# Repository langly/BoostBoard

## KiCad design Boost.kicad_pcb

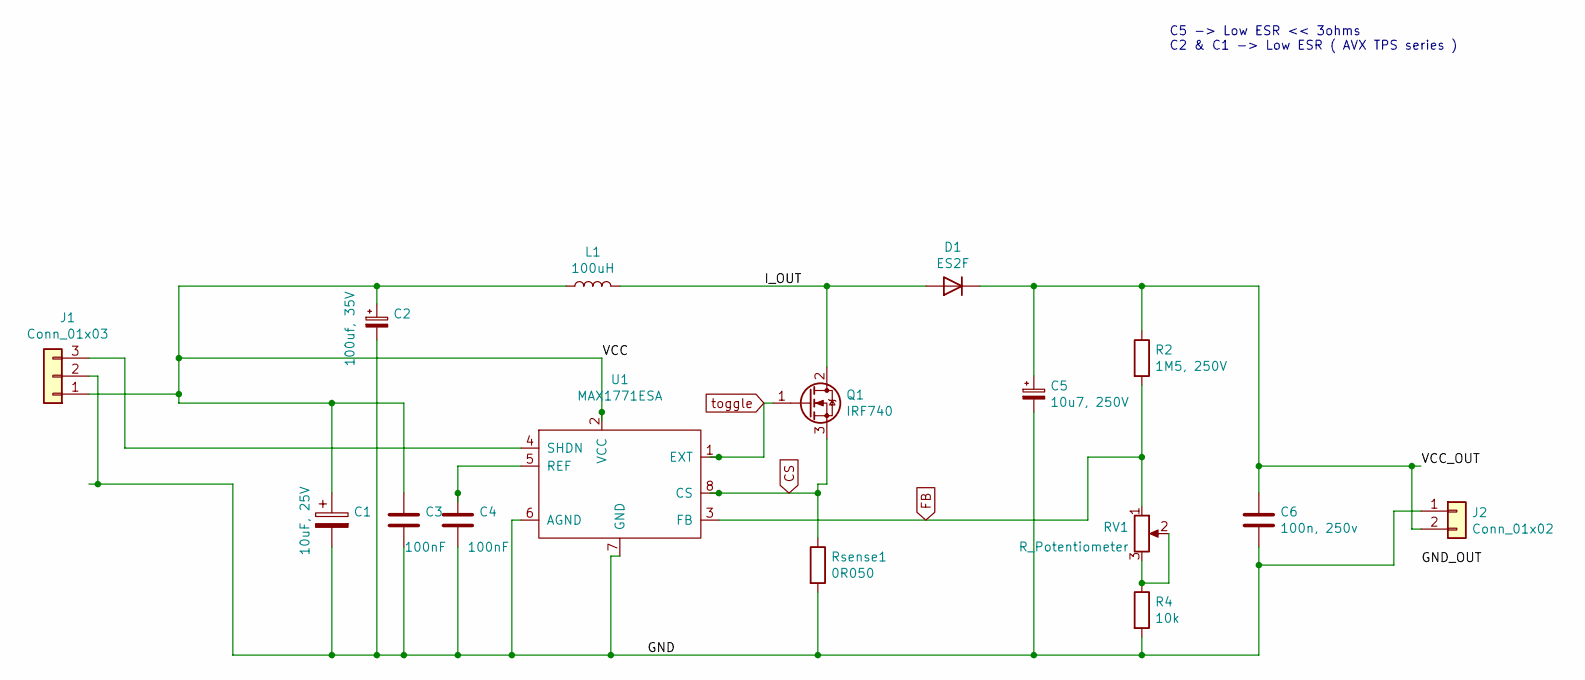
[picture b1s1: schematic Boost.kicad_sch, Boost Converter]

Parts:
C1: 10uF, 25V; CP_EIA-3528-21_Kemet-B_Pad1.50x2.35mm_HandSolder
C2: 100uf, 35V; CP_EIA-7361-38_AVX-V_Pad2.18x3.30mm_HandSolder
C3, C4: 100nF; C_0805_2012Metric
C5: 10u7, 250V; Panasonic-G17
C6: 100n, 250v; ECWU_B
D1: ES2F; D_SMB_Handsoldering
J1: Conn_01x03; 691412320003
J2: Conn_01x02; 691412320002
L1: 100uH; B82479A1
Q1: IRF740; TO-263-3_TabPin2
R2: 1M5, 250V; R_2512_6332Metric
R4: 10k; R_0805_2012Metric_Pad1.20x1.40mm_HandSolder
RV1: R_Potentiometer; 3214W1502E
Rsense1: 0R050; R_2010_5025Metric_Pad1.40x2.65mm_HandSolder
U1: MAX1771ESA; SOIC-8-1EP_3.9x4.9mm_P1.27mm_EP2.29x3mm

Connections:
/GND: C1.2, C2.2, C3.2, C4.2, C5.2, C6.2, J1.2, J2.1, R4.2, Rsense1.2, U1.6 (AGND), U1.7 (GND)
/I_OUT: D1.2 (A), L1.2, Q1.2 (D)
/VCC: C1.1, C2.1, C3.1, J1.1, L1.1, U1.2 (VCC)
/VCC_OUT: C5.1, C6.1, D1.1 (K), J2.2, R2.1
CS: Q1.3 (S), Rsense1.1, U1.8 (CS)
FB: R2.2, RV1.1, U1.3 (FB)
unnamed: J1.3, U1.4 (SHDN)
unnamed: R4.1, RV1.2, RV1.3
unnamed: C4.1, U1.5 (REF)
toggle: Q1.1 (G), U1.1 (EXT)

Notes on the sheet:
C5 -> Low ESR << 3ohms C2 & C1 -> Low ESR ( AVX TPS series )

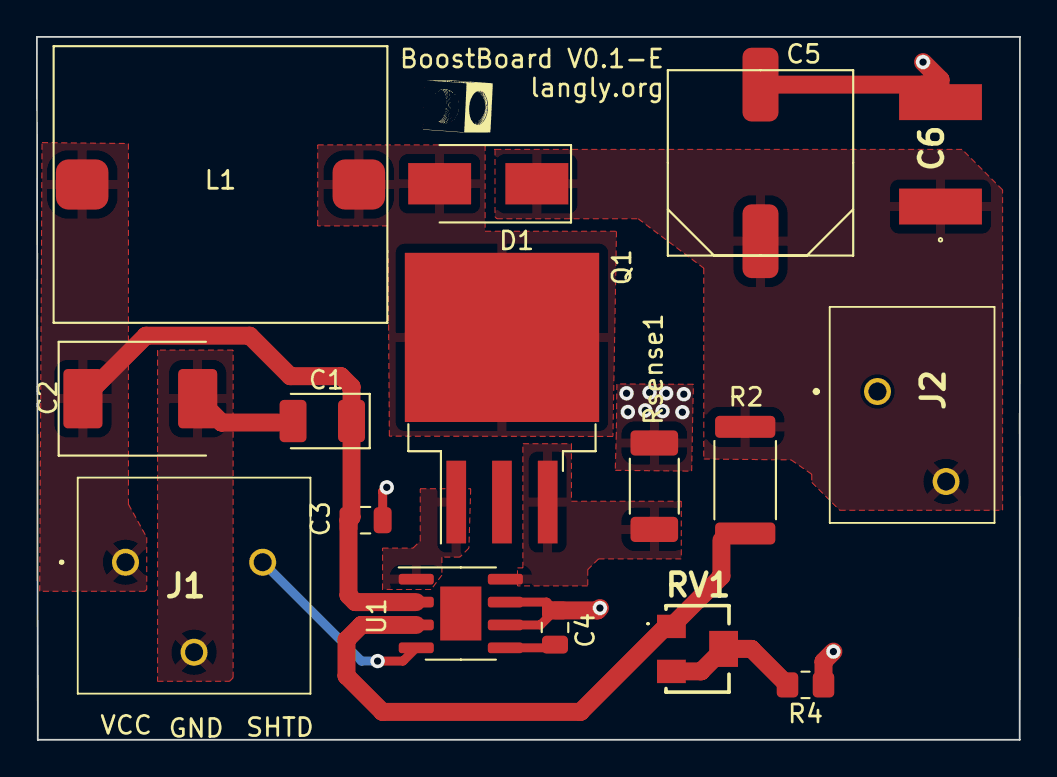
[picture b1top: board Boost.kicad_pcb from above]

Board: 2 copper layers, 54.6 x 39.0 mm, 16 parts (0 on the bottom side), 10 nets.

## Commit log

2024-03-14 Initial
2024-03-19 Added version v0.1-D
    - Moved stuff much closer
    - Increased the width of the traces
2024-03-27 Working on revision 0.1-E
